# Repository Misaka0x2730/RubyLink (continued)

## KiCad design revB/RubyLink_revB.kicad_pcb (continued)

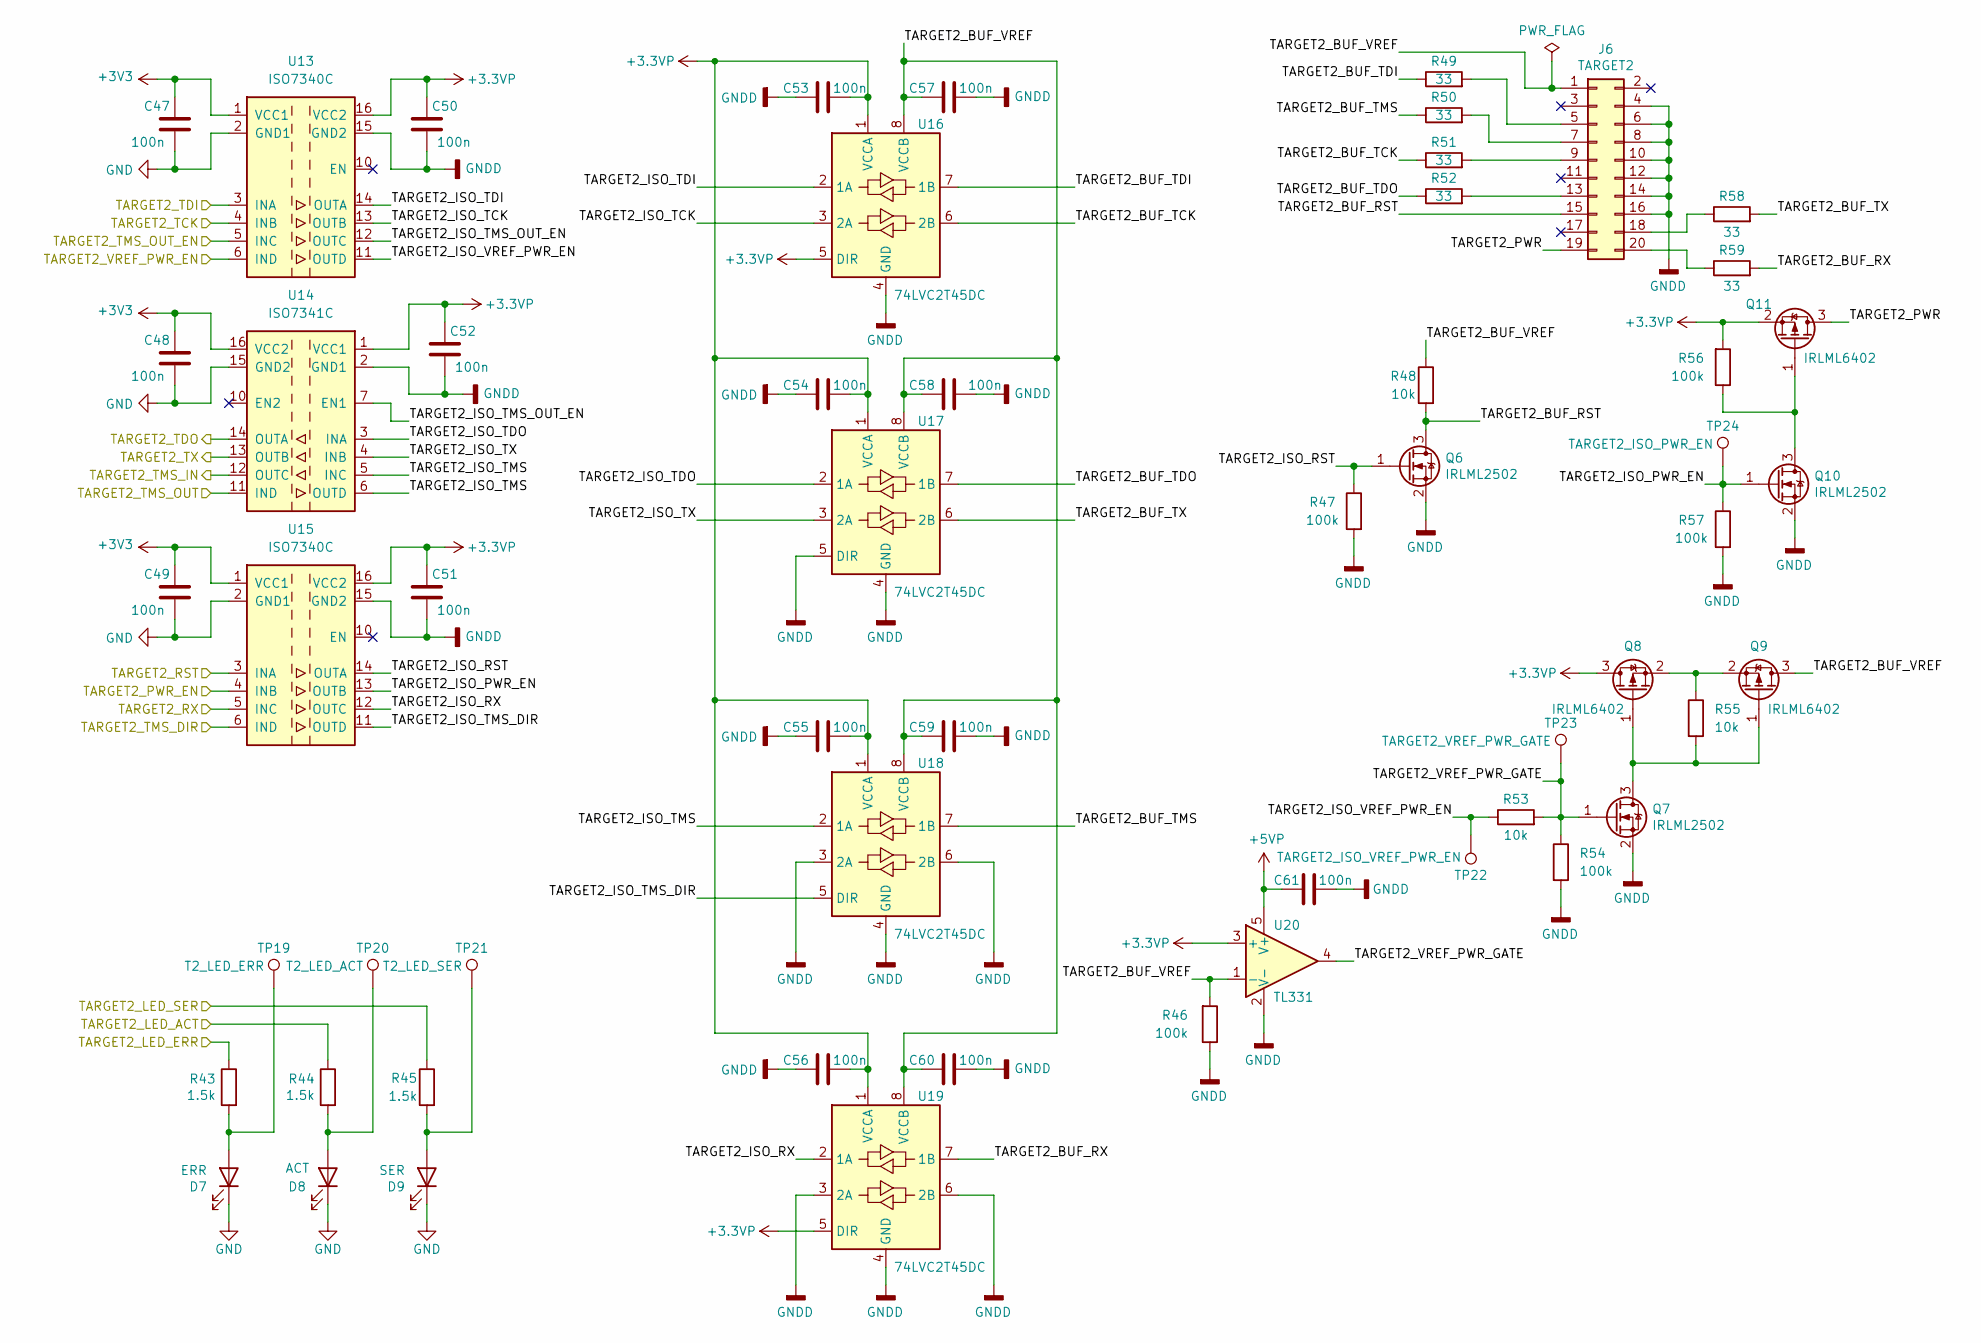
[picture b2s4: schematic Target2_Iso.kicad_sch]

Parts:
C47, C48, C49, C50, C51, C52, C53, C54, C55, C56, C57, C58, C59, C60: 100n; C_0402_1005Metric; Part Number CC0402KRX7R7BB104
C61: 100n; C_0402_1005Metric
D7: ERR; LED_D3.0mm
D8: ACT; LED_D3.0mm
D9: SER; LED_D3.0mm; Part Number FYLS-0603UYC
J6: TARGET2; IDC-Header_2x10_P2.54mm_Horizontal; Part Number BH-20R
Q6, Q7, Q10: IRLML2502; SOT-23; Part Number IRLML2502TRPBF
Q8, Q9, Q11: IRLML6402; SOT-23
R43, R44, R45: 1.5k; R_0402_1005Metric; Part Number RC0402FR-071K5L
R46, R54, R56: 100k; R_0402_1005Metric
R47, R57: 100k; R_0402_1005Metric; Part Number RC0402FR-0710KL
R48: 10k; R_0402_1005Metric; Part Number RC0402FR-0710KL
R49, R50, R51, R52, R58, R59: 33; R_0402_1005Metric; Part Number RC0402FR-07100KL
R53, R55: 10k; R_0402_1005Metric
TP19: T2_LED_ERR; TestPoint_Pad_D1.0mm
TP20: T2_LED_ACT; TestPoint_Pad_D1.0mm
TP21: T2_LED_SER; TestPoint_Pad_D1.0mm
TP22: TARGET2_ISO_VREF_PWR_EN; TestPoint_Pad_D1.0mm
TP23: TARGET2_VREF_PWR_GATE; TestPoint_Pad_D1.0mm
TP24: TARGET2_ISO_PWR_EN; TestPoint_Pad_D1.0mm
U13, U15: ISO7340C; SOIC-16W_7.5x10.3mm_P1.27mm
U14: ISO7341C; SOIC-16W_7.5x10.3mm_P1.27mm
U16, U17, U18, U19: 74LVC2T45DC; VSSOP-8_2.3x2mm_P0.5mm; Part Number SN74LVC2T45DCUR
U20: TL331; SOT-23-5

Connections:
+3.3VP: C50.2, C51.2, C52.2, C53.2, C54.2, C55.2, C56.2, Q8.3 (D), Q11.2 (S), R56.2, U13.16 (VCC2), U14.1 (VCC1), U15.16 (VCC2), U16.1 (VCCA), U16.5 (DIR), U17.1 (VCCA), U18.1 (VCCA), U19.1 (VCCA), U19.5 (DIR), U20.3 (+); also elsewhere on the board
+3V3: C47.2, C48.2, C49.2, U13.1 (VCC1), U14.16 (VCC2), U15.1 (VCC1); also elsewhere on the board
+5VP: C61.1, U20.5 (V+); also elsewhere on the board
/MCU/TARGET2_LED_ACT: R44.1; also elsewhere on the board
/MCU/TARGET2_LED_ERR: R43.1; also elsewhere on the board
/MCU/TARGET2_LED_SER: R45.1; also elsewhere on the board
/MCU/TARGET2_PWR_EN: U15.4 (INB); also elsewhere on the board
/MCU/TARGET2_RST: U15.3 (INA); also elsewhere on the board
/MCU/TARGET2_RX: U14.13 (OUTB); also elsewhere on the board
/MCU/TARGET2_TCK: U13.4 (INB); also elsewhere on the board
/MCU/TARGET2_TDI: U13.3 (INA); also elsewhere on the board
/MCU/TARGET2_TDO: U14.14 (OUTA); also elsewhere on the board
/MCU/TARGET2_TMS_DIR: U15.6 (IND); also elsewhere on the board
/MCU/TARGET2_TMS_IN: U14.12 (OUTC); also elsewhere on the board
/MCU/TARGET2_TMS_OUT: U14.11 (IND); also elsewhere on the board
/MCU/TARGET2_TMS_OUT_EN: U13.5 (INC); also elsewhere on the board
/MCU/TARGET2_TX: U15.5 (INC); also elsewhere on the board
/MCU/TARGET2_VREF_PWR_EN: U13.6 (IND); also elsewhere on the board
/Target2_Iso/TARGET2_BUF_RST: J6.15, Q6.3 (D), R48.2
/Target2_Iso/TARGET2_BUF_RX: R59.2, U19.7 (1B)
/Target2_Iso/TARGET2_BUF_TCK: R51.1, U16.6 (2B)
/Target2_Iso/TARGET2_BUF_TDI: R49.1, U16.7 (1B)
/Target2_Iso/TARGET2_BUF_TDO: R52.1, U17.7 (1B)
/Target2_Iso/TARGET2_BUF_TMS: R50.1, U18.7 (1B)
/Target2_Iso/TARGET2_BUF_TX: R58.2, U17.6 (2B)
/Target2_Iso/TARGET2_BUF_VREF: C57.2, C58.2, C59.2, C60.2, J6.1, Q9.3 (D), R46.2, R48.1, U16.8 (VCCB), U17.8 (VCCB), U18.8 (VCCB), U19.8 (VCCB), U20.1 (-)
/Target2_Iso/TARGET2_ISO_PWR_EN: Q10.1 (G), R57.1, TP24.1, U15.13 (OUTB)
/Target2_Iso/TARGET2_ISO_RST: Q6.1 (G), R47.1, U15.14 (OUTA)
/Target2_Iso/TARGET2_ISO_RX: U15.12 (OUTC), U19.2 (1A)
/Target2_Iso/TARGET2_ISO_TCK: U13.13 (OUTB), U16.3 (2A)
/Target2_Iso/TARGET2_ISO_TDI: U13.14 (OUTA), U16.2 (1A)
/Target2_Iso/TARGET2_ISO_TDO: U14.3 (INA), U17.2 (1A)
/Target2_Iso/TARGET2_ISO_TMS: U14.5 (INC), U14.6 (OUTD), U18.2 (1A)
/Target2_Iso/TARGET2_ISO_TMS_DIR: U15.11 (OUTD), U18.5 (DIR)
/Target2_Iso/TARGET2_ISO_TMS_OUT_EN: U13.12 (OUTC), U14.7 (EN1)
/Target2_Iso/TARGET2_ISO_TX: U14.4 (INB), U17.3 (2A)
/Target2_Iso/TARGET2_ISO_VREF_PWR_EN: R53.1, TP22.1, U13.11 (OUTD)
/Target2_Iso/TARGET2_PWR: J6.19, Q11.3 (D)
/Target2_Iso/TARGET2_VREF_PWR_GATE: Q7.1 (G), R53.2, R54.1, TP23.1, U20.4
GND: C47.1, C48.1, C49.1, D7.1 (K), D8.1 (K), D9.1 (K), U13.2 (GND1), U13.8 (GND1), U14.9 (GND2), U14.15 (GND2), U15.2 (GND1), U15.8 (GND1); also elsewhere on the board
GNDD: C50.1, C51.1, C52.1, C53.1, C54.1, C55.1, C56.1, C57.1, C58.1, C59.1, C60.1, C61.2, J6.4, J6.6, J6.8, J6.10, J6.12, J6.14, J6.16, Q6.2 (S), Q7.2 (S), Q10.2 (S), R46.1, R47.2, R54.2, R57.2, U13.9 (GND2), U13.15 (GND2), U14.2 (GND1), U14.8 (GND1), U15.9 (GND2), U15.15 (GND2), U16.4 (GND), U17.4 (GND), U17.5 (DIR), U18.3 (2A), U18.4 (GND), U18.6 (2B), U19.3 (2A), U19.4 (GND), U19.6 (2B), U20.2 (V-); also elsewhere on the board
unnamed: D7.2 (A), R43.2, TP19.1
unnamed: D8.2 (A), R44.2, TP20.1
unnamed: D9.2 (A), R45.2, TP21.1
unnamed: J6.5, R49.2
unnamed: J6.7, R50.2
unnamed: J6.9, R51.2
unnamed: J6.13, R52.2
unnamed: J6.18, R58.1
unnamed: J6.20, R59.1
unnamed: Q7.3 (D), Q8.1 (G), Q9.1 (G), R55.2
unnamed: Q8.2 (S), Q9.2 (S), R55.1
unnamed: Q10.3 (D), Q11.1 (G), R56.1

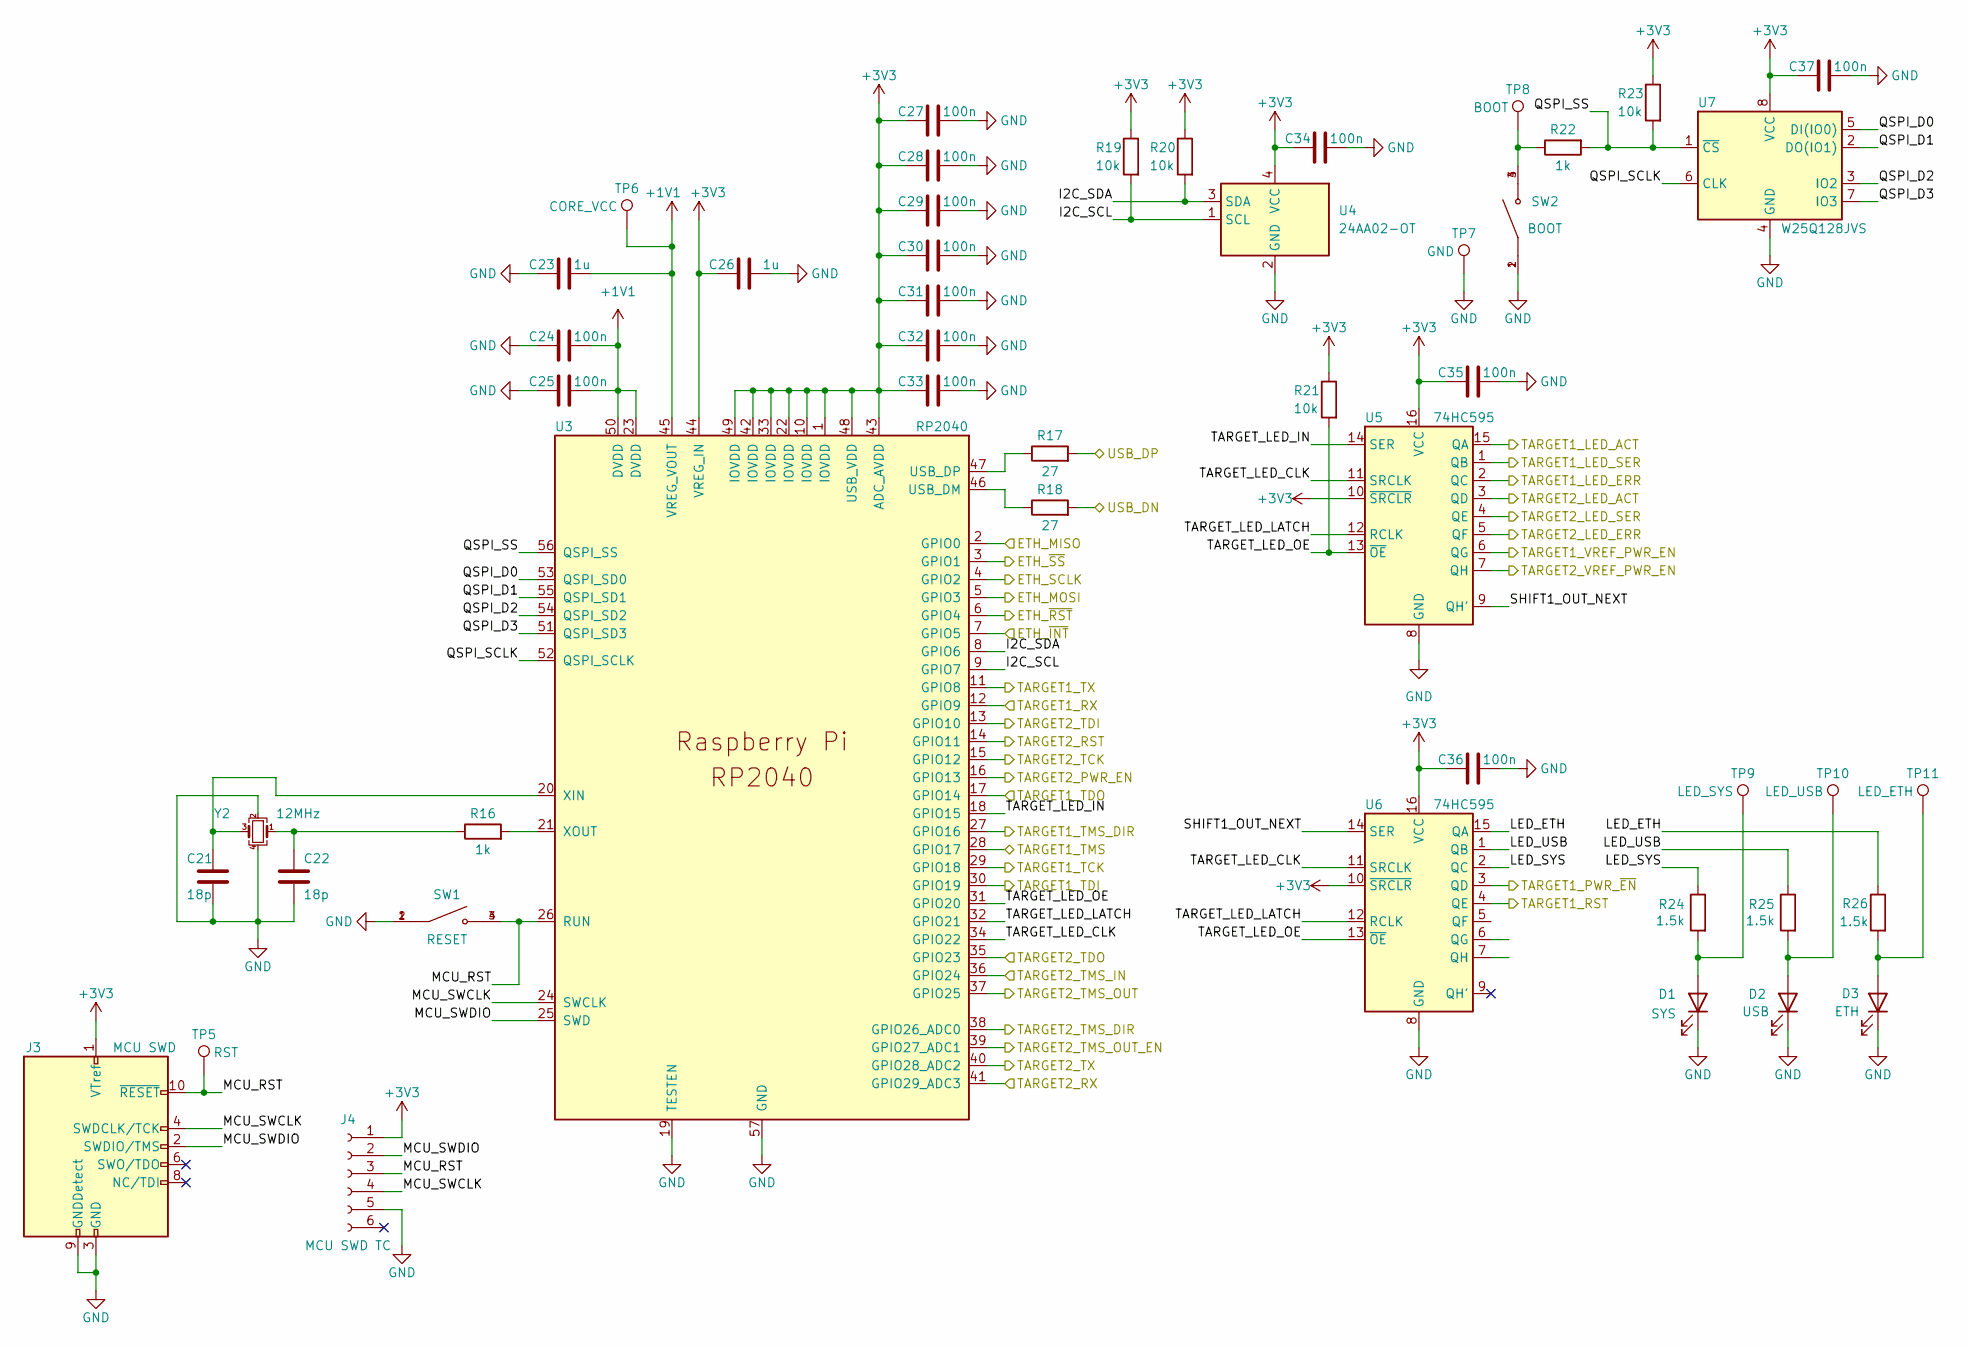
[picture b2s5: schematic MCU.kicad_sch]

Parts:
C21, C22: 18p; C_0402_1005Metric
C23, C26: 1u; C_0402_1005Metric
C24, C25, C27, C28, C29, C30, C31, C32, C33, C34, C35, C36, C37: 100n; C_0402_1005Metric
D1: SYS; LED_D3.0mm
D2: USB; LED_D3.0mm
D3: ETH; LED_D3.0mm; Part Number FYLS-0603UYC
J3: MCU SWD; IDC-Header_2x05_P2.54mm_Vertical
J4: MCU SWD TC; Tag-Connect_TC2030-IDC-FP_2x03_P1.27mm_Vertical
R16, R22: 1k; R_0402_1005Metric
R17, R18: 27; R_0402_1005Metric
R19, R20, R21, R23: 10k; R_0402_1005Metric
R24, R25, R26: 1.5k; R_0402_1005Metric; Part Number RC0402FR-071K5L
SW1: RESET; SW_1571563-9
SW2: BOOT; SW_1571563-9
TP5: RST; TestPoint_Pad_D1.0mm
TP6: CORE_VCC; TestPoint_Pad_D1.0mm
TP7: GND; TestPoint_Pad_D1.0mm
TP8: BOOT; TestPoint_Pad_D1.0mm
TP9: LED_SYS; TestPoint_Pad_D1.0mm
TP10: LED_USB; TestPoint_Pad_D1.0mm
TP11: LED_ETH; TestPoint_Pad_D1.0mm
U3: RP2040; RP2040-QFN-56
U4: 24AA02-OT; SOT-23-5
U5, U6: 74HC595; SOIC-16_3.9x9.9mm_P1.27mm
U7: W25Q128JVS; SOIC-8_5.23x5.23mm_P1.27mm
Y2: 12MHz; Crystal_SMD_3225-4Pin_3.2x2.5mm

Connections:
+1V1: C23.2, C24.2, C25.2, TP6.1, U3.23 (DVDD), U3.45 (VREG_VOUT), U3.50 (DVDD)
+3V3: C26.1, C27.1, C28.1, C29.1, C30.1, C31.1, C32.1, C33.1, C34.1, C35.1, C36.1, C37.1, J3.1 (VTref), J4.1, R19.1, R20.1, R21.1, R23.1, U3.1 (IOVDD), U3.10 (IOVDD), U3.22 (IOVDD), U3.33 (IOVDD), U3.42 (IOVDD), U3.43 (ADC_AVDD), U3.44 (VREG_IN), U3.48 (USB_VDD), U3.49 (IOVDD), U4.4 (VCC), U5.10 (~SRCLR), U5.16 (VCC), U6.10 (~SRCLR), U6.16 (VCC), U7.8 (VCC); also elsewhere on the board
/Input interfaces/ETH_MISO: U3.2 (GPIO0); also elsewhere on the board
/Input interfaces/ETH_MOSI: U3.5 (GPIO3); also elsewhere on the board
/Input interfaces/ETH_SCLK: U3.4 (GPIO2); also elsewhere on the board
/Input interfaces/ETH_~INT: U3.7 (GPIO5); also elsewhere on the board
/Input interfaces/ETH_~RST: U3.6 (GPIO4); also elsewhere on the board
/Input interfaces/ETH_~SS: U3.3 (GPIO1); also elsewhere on the board
/Input interfaces/USB_DN: R18.2; also elsewhere on the board
/Input interfaces/USB_DP: R17.2; also elsewhere on the board
/MCU/I2C_SCL: R19.2, U3.9 (GPIO7), U4.1 (SCL)
/MCU/I2C_SDA: R20.2, U3.8 (GPIO6), U4.3 (SDA)
/MCU/LED_ETH: R26.1, U6.15 (QA)
/MCU/LED_SYS: R24.1, U6.2 (QC)
/MCU/LED_USB: R25.1, U6.1 (QB)
/MCU/MCU_RST: J3.10 (~RESET), J4.3, SW1.3, SW1.4, TP5.1, U3.26 (RUN)
/MCU/MCU_SWCLK: J3.4 (SWDCLK/TCK), J4.4, U3.24 (SWCLK)
/MCU/MCU_SWDIO: J3.2 (SWDIO/TMS), J4.2, U3.25 (SWD)
/MCU/QSPI_D0: U3.53 (QSPI_SD0), U7.5 (DI(IO0))
/MCU/QSPI_D1: U3.55 (QSPI_SD1), U7.2 (DO(IO1))
/MCU/QSPI_D2: U3.54 (QSPI_SD2), U7.3 (IO2)
/MCU/QSPI_D3: U3.51 (QSPI_SD3), U7.7 (IO3)
/MCU/QSPI_SCLK: U3.52 (QSPI_SCLK), U7.6 (CLK)
/MCU/QSPI_SS: R22.2, R23.2, U3.56 (QSPI_SS), U7.1 (~CS)
/MCU/SHIFT1_OUT_NEXT: U5.9 (QH'), U6.14 (SER)
/MCU/TARGET1_LED_ACT: U5.15 (QA); also elsewhere on the board
/MCU/TARGET1_LED_ERR: U5.2 (QC); also elsewhere on the board
/MCU/TARGET1_LED_SER: U5.1 (QB); also elsewhere on the board
/MCU/TARGET1_PWR_~EN: U6.3 (QD); also elsewhere on the board
/MCU/TARGET1_RST: U6.4 (QE); also elsewhere on the board
/MCU/TARGET1_RX: U3.12 (GPIO9); also elsewhere on the board
/MCU/TARGET1_TCK: U3.29 (GPIO18); also elsewhere on the board
/MCU/TARGET1_TDI: U3.30 (GPIO19); also elsewhere on the board
/MCU/TARGET1_TDO: U3.17 (GPIO14); also elsewhere on the board
/MCU/TARGET1_TMS: U3.28 (GPIO17); also elsewhere on the board
/MCU/TARGET1_TMS_DIR: U3.27 (GPIO16); also elsewhere on the board
/MCU/TARGET1_TX: U3.11 (GPIO8); also elsewhere on the board
/MCU/TARGET1_VREF_PWR_EN: U5.6 (QG); also elsewhere on the board
/MCU/TARGET2_LED_ACT: U5.3 (QD); also elsewhere on the board
/MCU/TARGET2_LED_ERR: U5.5 (QF); also elsewhere on the board
/MCU/TARGET2_LED_SER: U5.4 (QE); also elsewhere on the board
/MCU/TARGET2_PWR_EN: U3.16 (GPIO13); also elsewhere on the board
/MCU/TARGET2_RST: U3.14 (GPIO11); also elsewhere on the board
/MCU/TARGET2_RX: U3.41 (GPIO29_ADC3); also elsewhere on the board
/MCU/TARGET2_TCK: U3.15 (GPIO12); also elsewhere on the board
/MCU/TARGET2_TDI: U3.13 (GPIO10); also elsewhere on the board
/MCU/TARGET2_TDO: U3.35 (GPIO23); also elsewhere on the board
/MCU/TARGET2_TMS_DIR: U3.38 (GPIO26_ADC0); also elsewhere on the board
/MCU/TARGET2_TMS_IN: U3.36 (GPIO24); also elsewhere on the board
/MCU/TARGET2_TMS_OUT: U3.37 (GPIO25); also elsewhere on the board
/MCU/TARGET2_TMS_OUT_EN: U3.39 (GPIO27_ADC1); also elsewhere on the board
/MCU/TARGET2_TX: U3.40 (GPIO28_ADC2); also elsewhere on the board
/MCU/TARGET2_VREF_PWR_EN: U5.7 (QH); also elsewhere on the board
/MCU/TARGET_LED_CLK: U3.34 (GPIO22), U5.11 (SRCLK), U6.11 (SRCLK)
/MCU/TARGET_LED_IN: U3.18 (GPIO15), U5.14 (SER)
/MCU/TARGET_LED_LATCH: U3.32 (GPIO21), U5.12 (RCLK), U6.12 (RCLK)
/MCU/TARGET_LED_OE: R21.2, U3.31 (GPIO20), U5.13 (~OE), U6.13 (~OE)
GND: C21.2, C22.2, C23.1, C24.1, C25.1, C26.2, C27.2, C28.2, C29.2, C30.2, C31.2, C32.2, C33.2, C34.2, C35.2, C36.2, C37.2, D1.1 (K), D2.1 (K), D3.1 (K), J3.3 (GND), J3.5 (GND), J3.9 (GNDDetect), J4.5, SW1.1, SW1.2, SW2.1, SW2.2, TP7.1, U3.19 (TESTEN), U3.57 (GND), U4.2 (GND), U5.8 (GND), U6.8 (GND), U7.4 (GND), Y2.2, Y2.4; also elsewhere on the board
unnamed: C21.1, U3.20 (XIN), Y2.3
unnamed: C22.1, R16.1, Y2.1
unnamed: D1.2 (A), R24.2, TP9.1
unnamed: D2.2 (A), R25.2, TP10.1
unnamed: D3.2 (A), R26.2, TP11.1
unnamed: R16.2, U3.21 (XOUT)
unnamed: R17.1, U3.47 (USB_DP)
unnamed: R18.1, U3.46 (USB_DM)
unnamed: R22.1, SW2.3, SW2.4, TP8.1

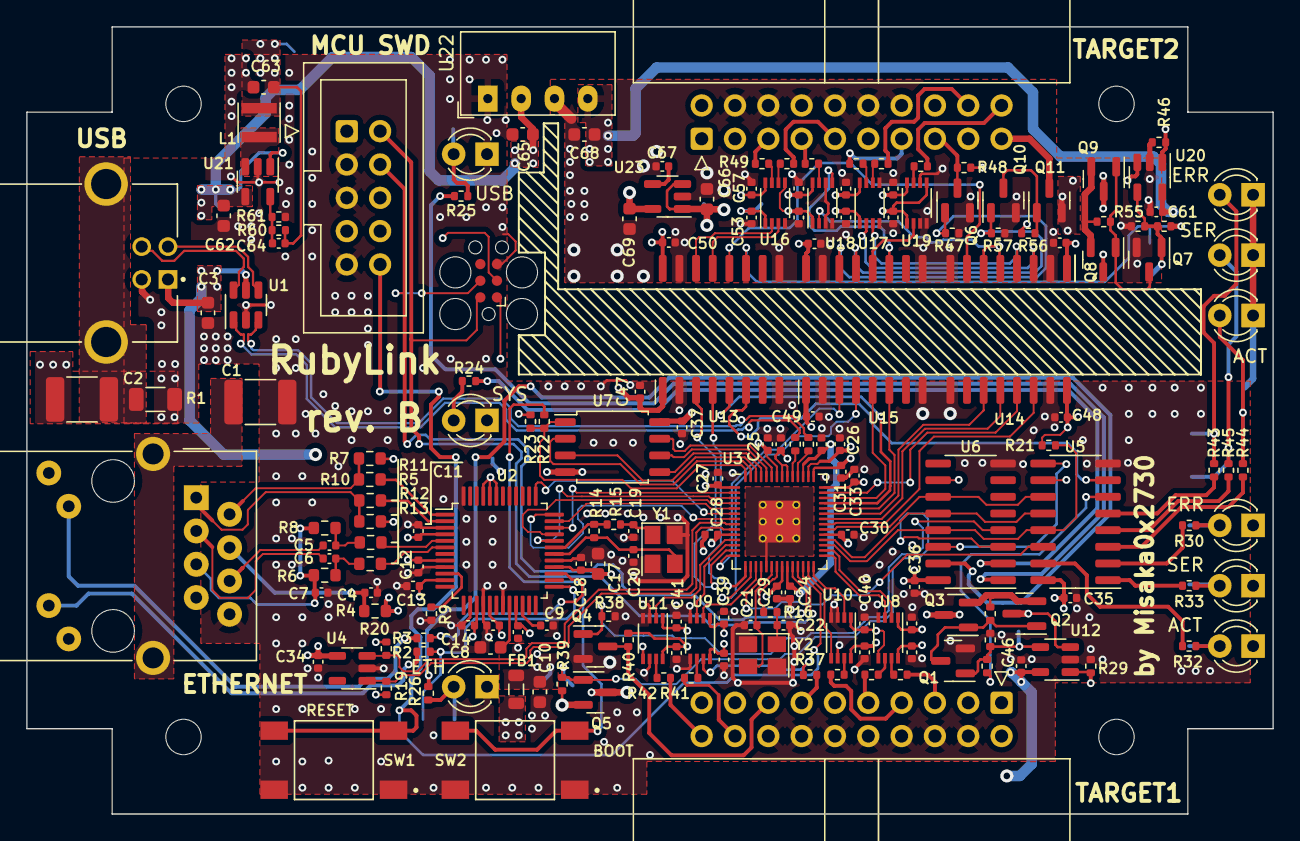
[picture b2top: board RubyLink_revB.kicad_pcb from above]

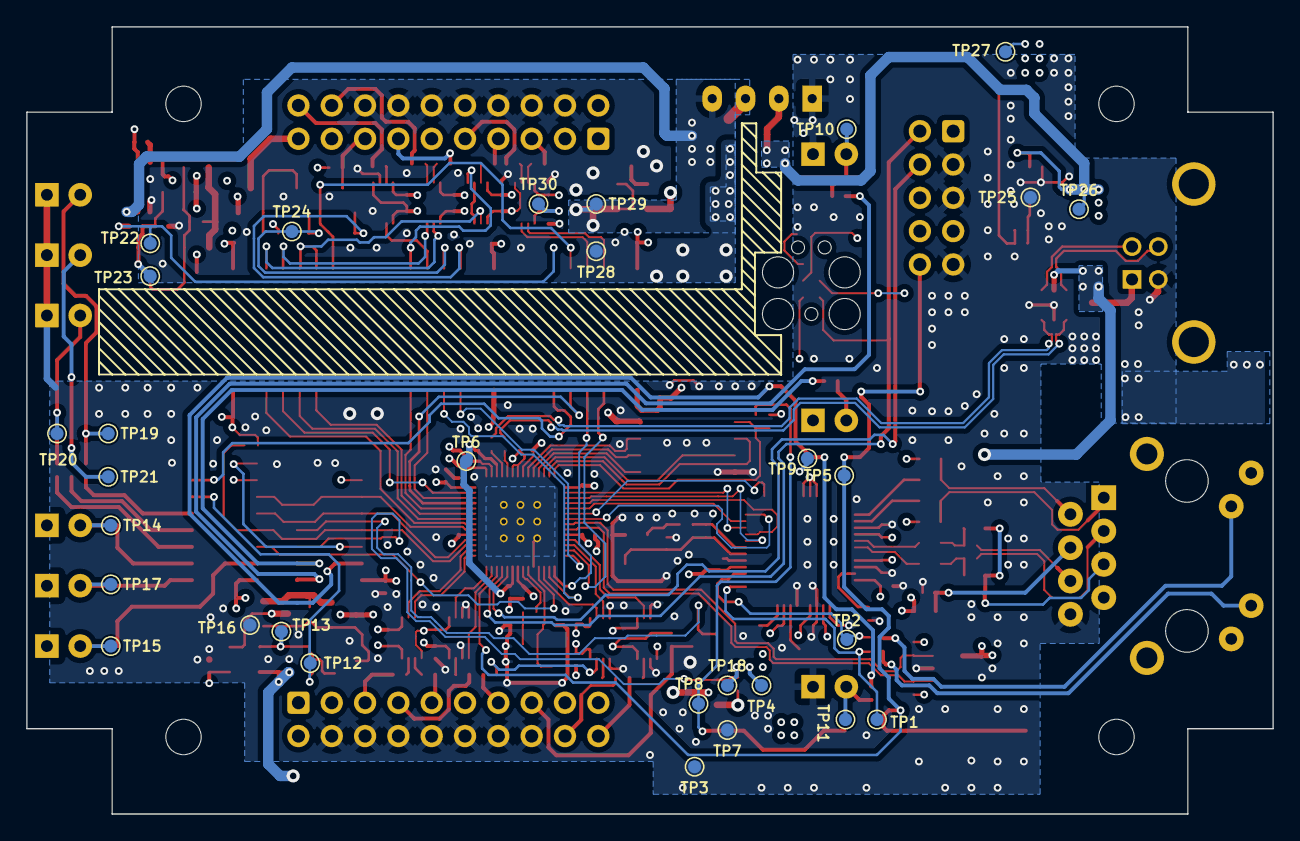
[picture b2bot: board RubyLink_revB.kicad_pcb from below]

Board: 4 copper layers, 95.0 x 60.0 mm, 219 parts (30 on the bottom side), 155 nets.

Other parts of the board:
REF1, REF2, REF3, REF4: MountingHole_2.7mm_M2.5

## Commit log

2021-08-15 Added schematic
    Added alpha-version of the schematic.
    Started PCB routing.
2021-08-18 Intermediate PCB routing results
2021-08-20 Pre-finished PCB version
    Pre-finished PCB version. Added 3D models for some components.
2021-08-21 Finished PCB routing
2021-10-10 Added final version and Gerber files.
2021-12-27 Create LICENSE
2022-08-15 Added revision B
    Revision B:
    Replaced SMD LEDs by THT LEDs;
    Replaced USB Type C by USB-B;
    Optimized pinout to be able to control the isolated interface through the second PIO.
    Placed TC2030 footprint on the PCB.
2023-01-09 Initial commit for revision C
2023-01-09 Initial commit for revC with battery
2023-01-09 Fixed prepared KSZ8851
2023-01-09 Prepared PCB for KSZ8851
2023-01-09 Pre-release PCB with KSZ8851 and battery charger
2023-01-09 Pre-release version with HR911105A and MIC2090 as current limiter
2023-01-09 Pre-released version with user button on the ADC channel
2023-01-09 Minor silk fixes
2023-01-09 Replaced LED resistors from 0603 to 0402, BOM simplification
2023-01-09 Pre-relased version with Si8645bb as digital isolators, replaced 74HC595 by TCA9535PWR, added buzzer
2023-01-09 Minor silk and bom fixes
